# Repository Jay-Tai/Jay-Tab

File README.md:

# The Jay-Tab!

.png>)
The Jay-Tab is one of my biggest personal projects! I made it to use it as a small screen to keep on my desk!

I made this project mainly out of personal interest. As to get the money to make this project in real life, I used [Hack club's stardance program!](https://stardance.hackclub.com/)

## Features!

There are many features that are packed into Jay-Tab:

- Beautifully 3D-Printed case!
- 2-Layer PCB enclosing all the hardware!
- Running on the ESP32-S3 WROOM
- 7.5" E-Ink touchscreen display to hold all the features of the Jay-Tab!
- <b>Home screen</b> that shows all you need to know at a glimpse
- <b>Calendar screen</b> that shows all the events happening in your day!
- <b>Timer screen</b> that has a timer that you can play a timer on a dedicated screen on your desk!
- <b>Home control screen</b> that is based off the Govee API, letting you toggle your lights, and change the color!

## CAD

The CAD model is from OnShape. It is made so the screen takes up 95% of the project, along with a stem that has weights inside of it to hold the Jay-Tab.

There are multiple parts, that are all going to be held using multiple screws. The power button is on the right side stem of the project.

### Important note about the CAD!

There is a part in the CAD that is CNCed. The bottom weight is CNCed to make sure that the Jay-Tab is able to stay upright, while also giving a premium feel through weight.There is also another laser-cuttable rubber part that goes on the bottom to stop it from moving.

.png>)

## PCB

The PCB is the main hub of the entire project. It is in charge of making the OLED work, running code, powering the project, and the switches. It runs based off of the ESP32-S3 WROOM.

The following image is the schematic:

And this is the PCB:

## Firmware

The firmware for the project is based off of [python](https://www.python.org/) coding language. I made the UI Drawing Interface by myself, as I couldn't find any good libraries that are simple, and are able to support E-Ink Displays. The firmware includes the following:

- Home page that has a glimpse of your entire day with upcoming events, time, and quick controls.
- Calendar panel that is connected to your Google Calendar that shows all your events in a day
- Timer panel that allows you to create timers
- Smart home panel that connects to the Govee API, allowing you to toggle and change the color of your Govee lights.

Here is what the pages look like when connected to my APIs:

### Home Page:

### Calendar:

### Timer:

### Home Control:

## Quick Start

To make your own Jay-Tab, it is <b>crucial</b> that you follow these steps so that everything works with your environment!

<u>1: Create your Google Calendar API!</u>
The first step to making your own Jay-Tab is to create your own Google Calendar API. You can use the Google Cloud Calender API by clicking [here](https://console.cloud.google.com/marketplace/product/google/calendar-json.googleapis.com?q=search&referrer=search&project=jay-tab). Download the file that has your key, and rename it to <i>calendar_desktop_credentials.json</i>

<u>2: Create your Govee API!</u>
The second step is to create the Govee API! Use the [following guide](https://developer.govee.com/docs/getting-started) to create your own govee API!

Once you get the Govee API, put it in under "apikey"

<u>3: Change your home screen name!</u>
To change the name on the Home Screen, use the adobe illustrator file that is attached under the software folder of the Jay-Tab. This will let you change the name from my name (Jay) to whatever it is!

# BOM

To make your own Jay-Tab, use the BOM under /bom.csv! :D

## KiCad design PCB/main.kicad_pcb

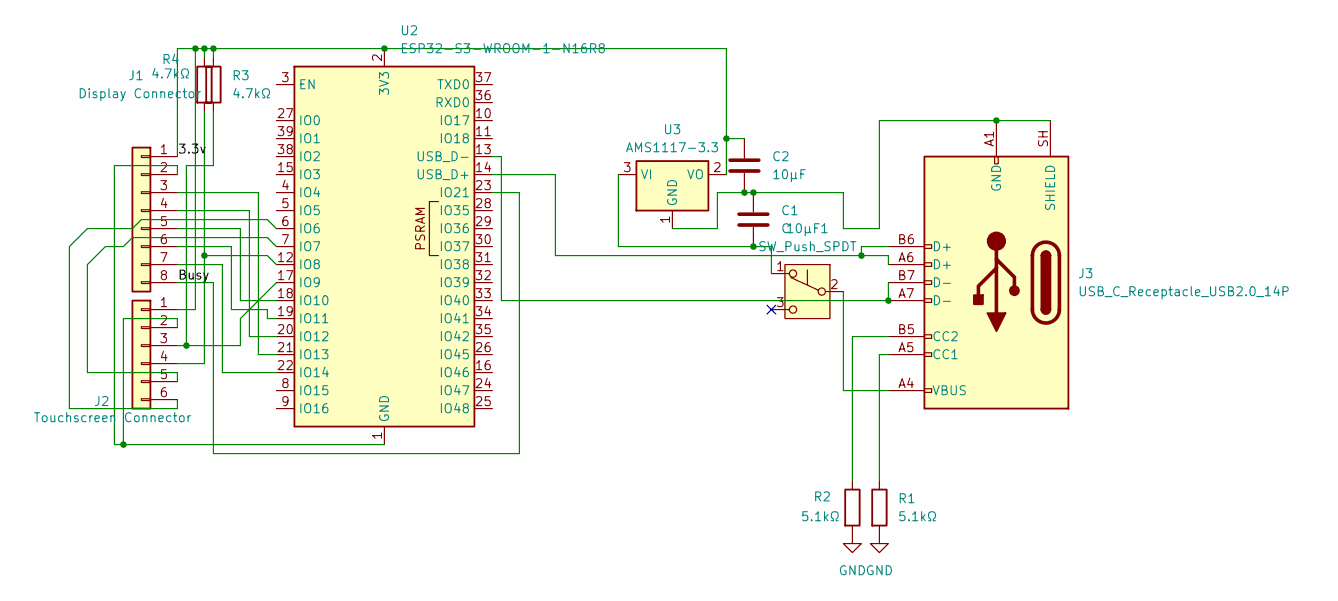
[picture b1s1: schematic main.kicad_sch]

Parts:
10μF1: SW_Push_SPDT; External_SPDT_Switch
C1: C; C_Disc_D5.0mm_W2.5mm_P5.00mm
C2: 10μF; C_Disc_D5.0mm_W2.5mm_P5.00mm
J1: Display Connector; PinSocket_1x08_P2.54mm_Vertical
J2: Touchscreen Connector; FPC_6pc_0.5mm_Breakout_Board_Pins
J3: USB_C_Receptacle_USB2.0_14P; External_USB_C
R1, R2: 5.1kΩ; R_Axial_DIN0207_L6.3mm_D2.5mm_P7.62mm_Horizontal
R3, R4: 4.7kΩ; R_Axial_DIN0207_L6.3mm_D2.5mm_P7.62mm_Horizontal
U2: ESP32-S3-WROOM-1-N16R8; ESP32-S3-WROOM-1
U3: AMS1117-3.3; SOT-223-3_TabPin2

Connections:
/3.3v: C2.2, J1.1, J2.1, R3.1, R4.1, U2.2 (3V3), U3.2 (VO)
/Busy: J1.8, U2.23 (IO21)
GND: R1.2, R2.2
unnamed: 10μF1.1 (A), C1.1, U3.3 (VI)
unnamed: 10μF1.2 (B), J3.A4 (VBUS), J3.A9 (VBUS), J3.B4 (VBUS), J3.B9 (VBUS)
unnamed: J1.2, J2.2, U2.1 (GND), U2.40 (GND), U2.41 (GND)
unnamed: J1.3, U2.21 (IO13)
unnamed: J1.4, U2.20 (IO12)
unnamed: J1.5, U2.18 (IO10)
unnamed: J1.6, U2.19 (IO11)
unnamed: J1.7, U2.22 (IO14)
unnamed: J2.3, R3.2, U2.17 (IO9)
unnamed: J2.4, R4.2, U2.12 (IO8)
unnamed: J2.5, U2.7 (IO7)
unnamed: J2.6, U2.6 (IO6)
unnamed: J3.A5 (CC1), R1.1
unnamed: J3.B5 (CC2), R2.1
unnamed: C1.2, C2.1, J3.A1 (GND), J3.A12 (GND), J3.B1 (GND), J3.B12 (GND), J3.SH (SHIELD), U3.1 (GND)
unnamed: J3.A6 (D+), J3.B6 (D+), U2.14 (USB_D+)
unnamed: J3.A7 (D-), J3.B7 (D-), U2.13 (USB_D-)

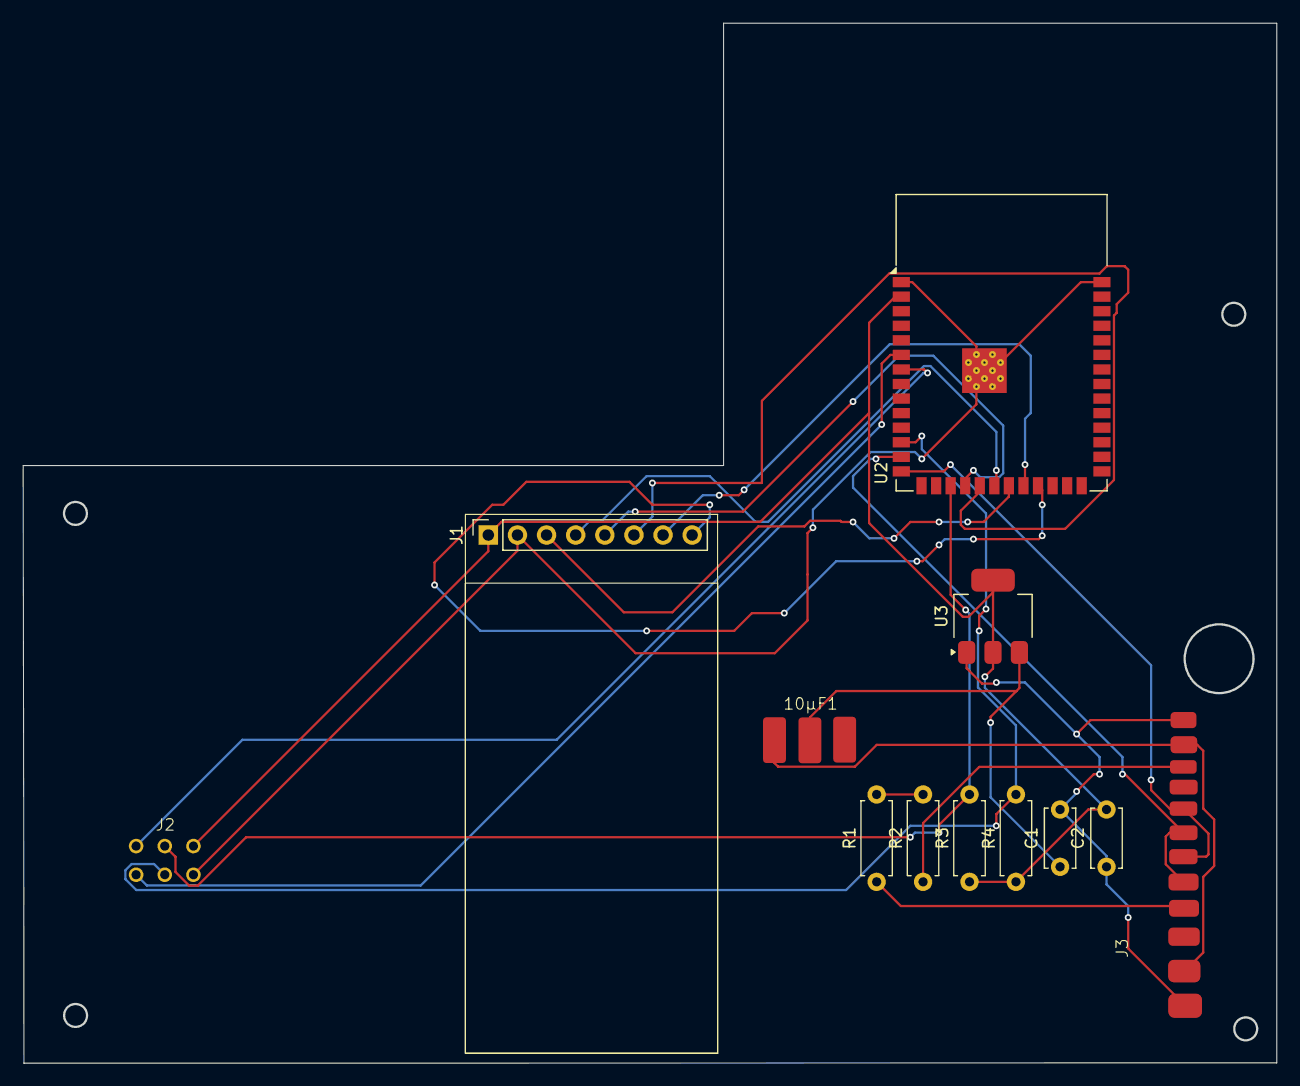
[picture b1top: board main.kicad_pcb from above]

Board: 2 copper layers, 109.3 x 90.7 mm, 12 parts (0 on the bottom side), 20 nets.
